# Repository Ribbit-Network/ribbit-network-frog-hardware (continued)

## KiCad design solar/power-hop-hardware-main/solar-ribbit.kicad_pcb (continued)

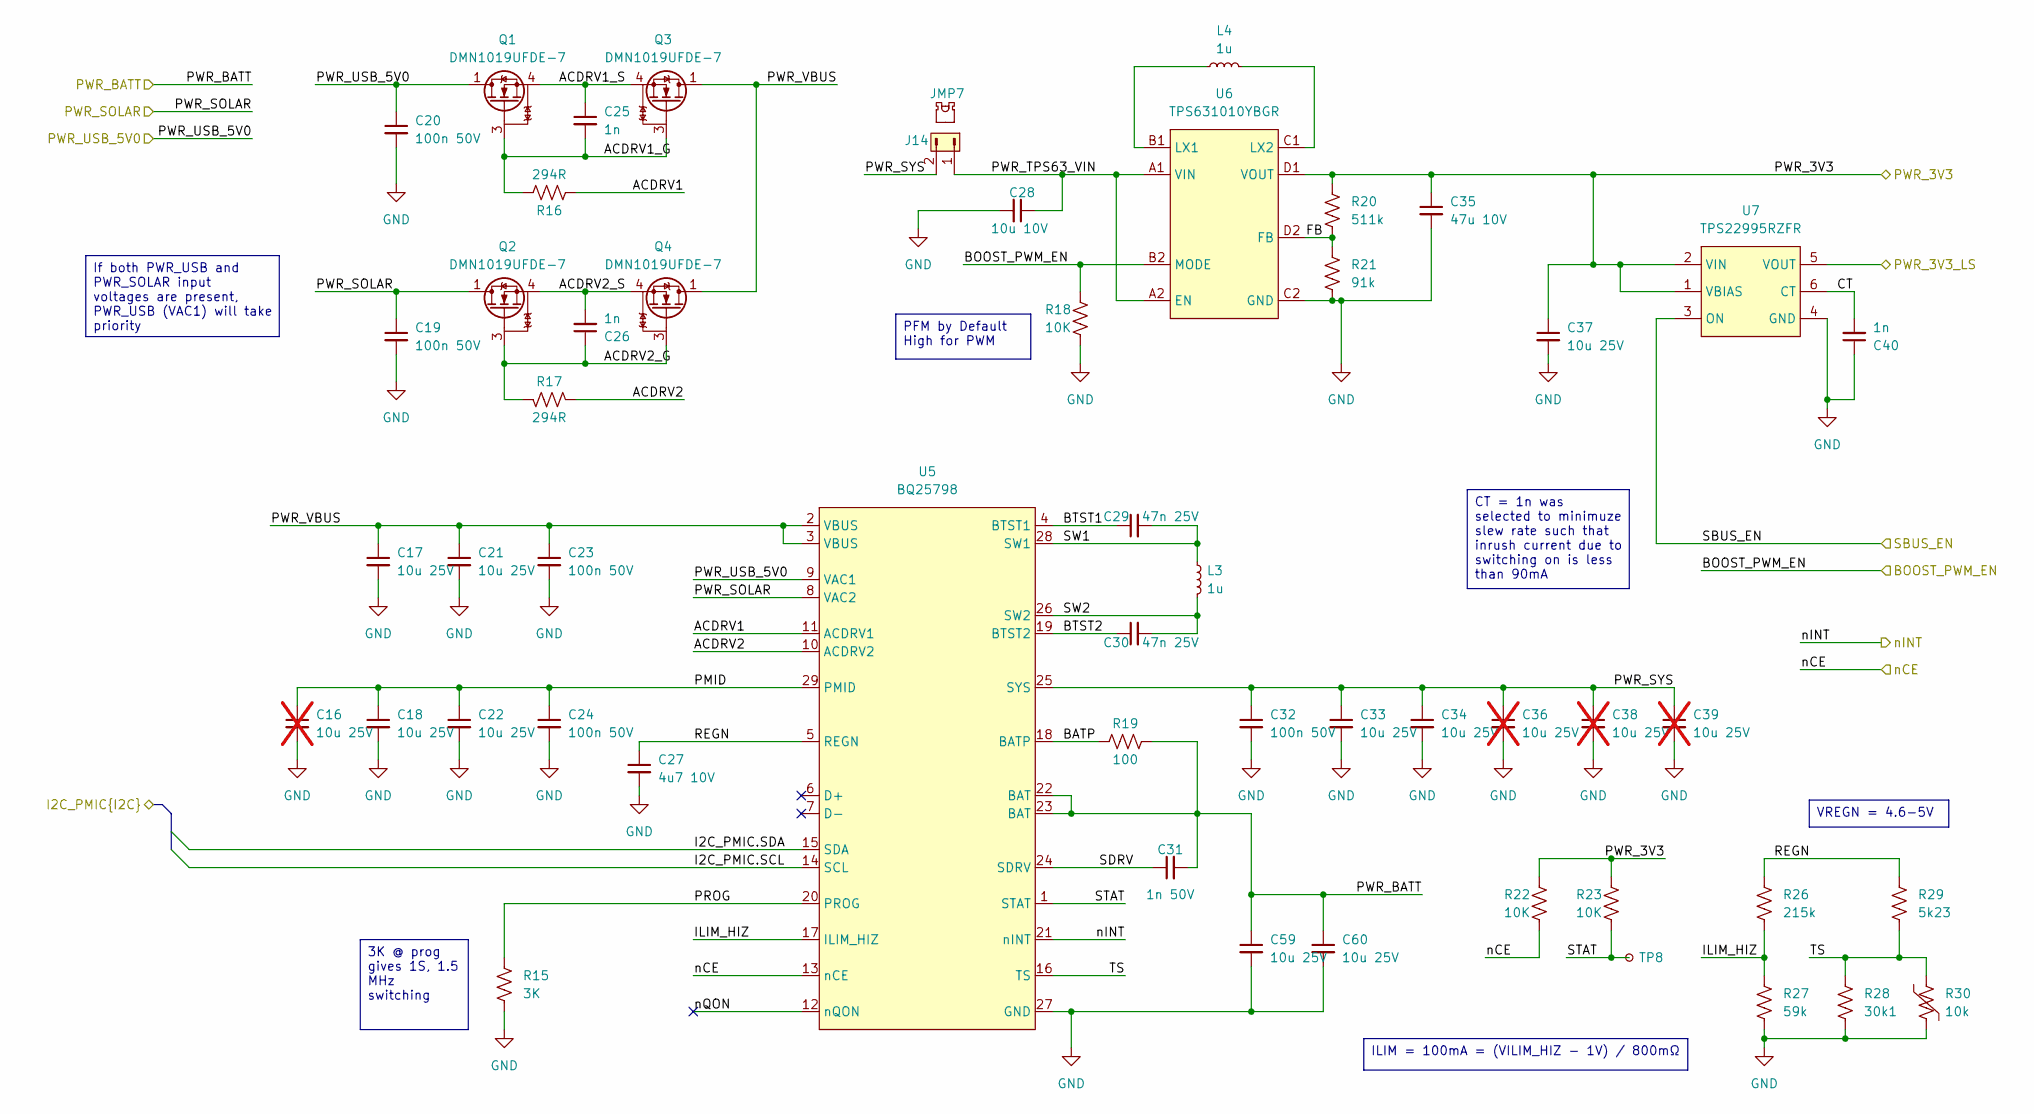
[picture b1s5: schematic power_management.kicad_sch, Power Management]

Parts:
C16, C36, C38, C39: 10u 25V; C_0805_2012Metric; MPN GRM21BR61E106KA73L; not fitted
C17, C18, C21, C22, C33, C34, C37, C59, C60: 10u 25V; C_0805_2012Metric; MPN GRM21BR61E106KA73L
C19, C20, C23, C24, C32: 100n 50V; C_0402_1005Metric; MPN GRM155R71H104KE14D
C25, C26, C40: 1n; C_0201_0603Metric; MPN GRM033R71E102KA01D
C27: 4u7 10V; C_0402_1005Metric; MPN GRM155R61A475MEAAD
C28: 10u 10V; C_0805_2012Metric; MPN C0805C106K8PACTU
C29, C30: 47n 25V; C_0402_1005Metric; MPN GRM155R71E473KA88D
C31: 1n 50V; C_0402_1005Metric; MPN GRM1555C1H102JA01D
C35: 47u 10V; C_0805_2012Metric; MPN GRM21BR61A476ME15K
J14: 10129380-902001BLF; PinHeader_1x02_P2.54mm_Vertical_SMD_Pin1Left; MPN 10129380-902001BLF
JMP7: QPC02SXGN-RC; MPN QPC02SXGN-RC
L3, L4: 1u; L_Taiyo-Yuden_MD-3030; MPN LSXND3030QKT1R0NNG
Q1, Q2, Q3, Q4: DMN1019UFDE-7; DI_DFN2020-6; MPN DMN1019UFDE-7
R15: 3K; R_0402_1005Metric; MPN ERJ-2RKF3001X
R16, R17: 294R; R_0402_1005Metric; MPN ERJ-2RKF2940X
R18, R22, R23: 10K; R_0402_1005Metric; MPN ERJ-2RKF1002X
R19: 100; R_0402_1005Metric; MPN ERJ-2RKF1000X
R20: 511k; R_0402_1005Metric; MPN CRCW0402511KFKEDC
R21: 91k; R_0402_1005Metric; MPN ERJ-2RKF9102X
R26: 215k; R_0402_1005Metric; MPN RC0402FR-07215KL
R27: 59k; R_0402_1005Metric; MPN RC0402FR-0759KL
R28: 30k1; R_0402_1005Metric; MPN RC0402FR-0730K1L
R29: 5k23; R_0402_1005Metric; MPN RC0402FR-075K23L
R30: 10k; R_0402_1005Metric; MPN NTCG103JF103FT1
TP8: TestPoint_Small; TestPoint_Pad_1.0x1.0mm; Part-DB ID 144
U5: BQ25798; TI_VQFN-HR-29; MPN BQ25798RQMR
U6: TPS631010YBGR; TI_DSBGA-8; MPN TPS631010YBGR
U7: TPS22995RZFR; TI_WQFN-6; MPN TPS22995RZFR

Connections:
/BOOST_PWM_EN: R18.1, U6.B2 (MODE); also elsewhere on the board
/BQ_nCE: R22.2, U5.13 (nCE); also elsewhere on the board
/BQ_nINT: U5.21 (nINT); also elsewhere on the board
/PWR_3V3: C35.1, C37.1, R20.1, R22.1, R23.1, U6.D1 (VOUT), U7.1 (VBIAS), U7.2 (VIN); also elsewhere on the board
/PWR_3V3_LS: U7.5 (VOUT); also elsewhere on the board
/PWR_BATT: C31.2, C59.1, C60.1, R19.2, U5.22 (BAT), U5.23 (BAT); also elsewhere on the board
/PWR_PANEL: C19.1, Q2.1 (D), U5.8 (VAC2); also elsewhere on the board
/PWR_USB: C20.1, Q1.1 (D), U5.9 (VAC1); also elsewhere on the board
/Power Management/ACDRV1: R16.2, U5.11 (ACDRV1)
/Power Management/ACDRV1_G: C25.2, Q1.3 (G), Q3.3 (G), R16.1
/Power Management/ACDRV1_S: C25.1, Q1.4 (S), Q3.4 (S)
/Power Management/ACDRV2: R17.2, U5.10 (ACDRV2)
/Power Management/ACDRV2_G: C26.1, Q2.3 (G), Q4.3 (G), R17.1
/Power Management/ACDRV2_S: C26.2, Q2.4 (S), Q4.4 (S)
/Power Management/BATP: R19.1, U5.18 (BATP)
/Power Management/BTST1: C29.1, U5.4 (BTST1)
/Power Management/BTST2: C30.1, U5.19 (BTST2)
/Power Management/CT: C40.2, U7.6 (CT)
/Power Management/FB: R20.2, R21.1, U6.D2 (FB)
/Power Management/I2C_PMIC.SCL: U5.14 (SCL); also elsewhere on the board
/Power Management/I2C_PMIC.SDA: U5.15 (SDA); also elsewhere on the board
/Power Management/ILIM_HIZ: R26.2, R27.1, U5.17 (ILIM_HIZ)
/Power Management/PMID: C16.1, C18.1, C22.1, C24.1, U5.29 (PMID)
/Power Management/PROG: R15.1, U5.20 (PROG)
/Power Management/PWR_SYS: C32.1, C33.1, C34.1, C36.1, C38.1, C39.1, J14.2, U5.25 (SYS)
/Power Management/PWR_TPS63_VIN: C28.1, J14.1, U6.A1 (VIN), U6.A2 (EN)
/Power Management/PWR_VBUS: C17.1, C21.1, C23.1, Q3.1 (D), Q4.1 (D), U5.2 (VBUS), U5.3 (VBUS)
/Power Management/REGN: C27.1, R26.1, R29.1, U5.5 (REGN)
/Power Management/SDRV: C31.1, U5.24 (SDRV)
/Power Management/STAT: R23.2, TP8.1, U5.1 (STAT)
/Power Management/SW1: C29.2, L3.1, U5.28 (SW1)
/Power Management/SW2: C30.2, L3.2, U5.26 (SW2)
/Power Management/TS: R28.1, R29.2, R30.1, U5.16 (TS)
/Power Management/nQON: U5.12 (nQON)
/SBUS_EN: U7.3 (ON); also elsewhere on the board
GND: C16.2, C17.2, C18.2, C19.2, C20.2, C21.2, C22.2, C23.2, C24.2, C27.2, C28.2, C32.2, C33.2, C34.2, C35.2, C36.2, C37.2, C38.2, C39.2, C40.1, C59.2, C60.2, R15.2, R18.2, R21.2, R27.2, R28.2, R30.2, U5.27 (GND), U6.C2 (GND), U7.4 (GND); also elsewhere on the board
unnamed: L4.1, U6.B1 (LX1)
unnamed: L4.2, U6.C1 (LX2)

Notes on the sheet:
ILIM = 100mA = (VILIM_HIZ - 1V) / 800mΩ
CT = 1n was selected to minimuze slew rate such that inrush current due to switching on is less than 90mA
If both PWR_USB and PWR_SOLAR input voltages are present, PWR_USB (VAC1) will take priority
VREGN = 4.6-5V
PFM by Default High for PWM
3K @ prog gives 1S, 1.5 MHz switching

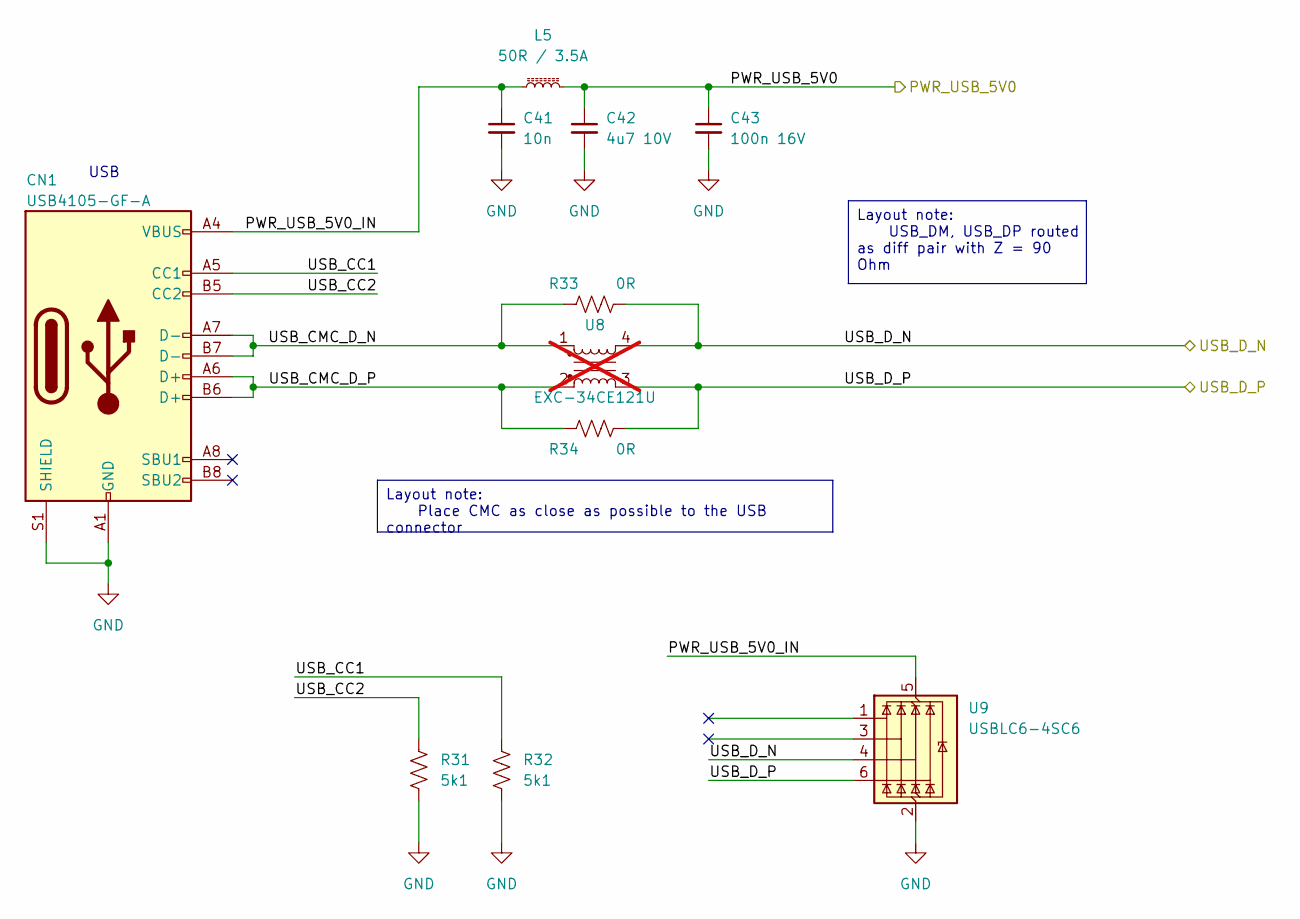
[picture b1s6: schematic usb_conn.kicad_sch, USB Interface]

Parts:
C41: 10n; C_0402_1005Metric; MPN CC0402KRX7R8BB103
C42: 4u7 10V; C_0402_1005Metric; MPN GRM155R61A475MEAAD
C43: 100n 16V; C_0402_1005Metric; MPN GRM155R71H104KE14D
CN1: USB4105-GF-A; GCT_USB4105-XX; MPN USB4105-GF-A
L5: 50R / 3.5A; L_1206_3216Metric; MPN BLM31PG500SN1L
R31, R32: 5k1; R_0402_1005Metric; MPN ERJ-2RKF5101X
R33, R34: 0R; R_0402_1005Metric; MPN ERJ-2GE0R00X
U8: EXC-34CE121U; PANASONIC_EXCX4CE; MPN EXC-34CE121U; not fitted
U9: USBLC6-4SC6; ST_SOT-23-6; MPN USBLC6-4SC6

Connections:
/PWR_USB_IN: C42.1, C43.1, L5.2; also elsewhere on the board
/USB/PWR_USB_5V0_IN: C41.1, CN1.A4 (VBUS), CN1.A9 (VBUS), CN1.B4 (VBUS), CN1.B9 (VBUS), L5.1, U9.5 (VBUS)
/USB/USB_CC1: CN1.A5 (CC1), R32.1
/USB/USB_CC2: CN1.B5 (CC2), R31.1
/USB/USB_CMC_D_N: CN1.A7 (D-), CN1.B7 (D-), R33.1, U8.1
/USB/USB_CMC_D_P: CN1.A6 (D+), CN1.B6 (D+), R34.1, U8.2
/USB/USB_D_N: R33.2, U8.4, U9.4 (I/O3); also elsewhere on the board
/USB/USB_D_P: R34.2, U8.3, U9.6 (I/O4); also elsewhere on the board
GND: C41.2, C42.2, C43.2, CN1.A1 (GND), CN1.A12 (GND), CN1.B1 (GND), CN1.B12 (GND), CN1.S1 (SHIELD), R31.2, R32.2, U9.2 (GND); also elsewhere on the board

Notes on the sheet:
USB
Layout note: USB_DM, USB_DP routed as diff pair with Z = 90 Ohm
Layout note: Place CMC as close as possible to the USB connector

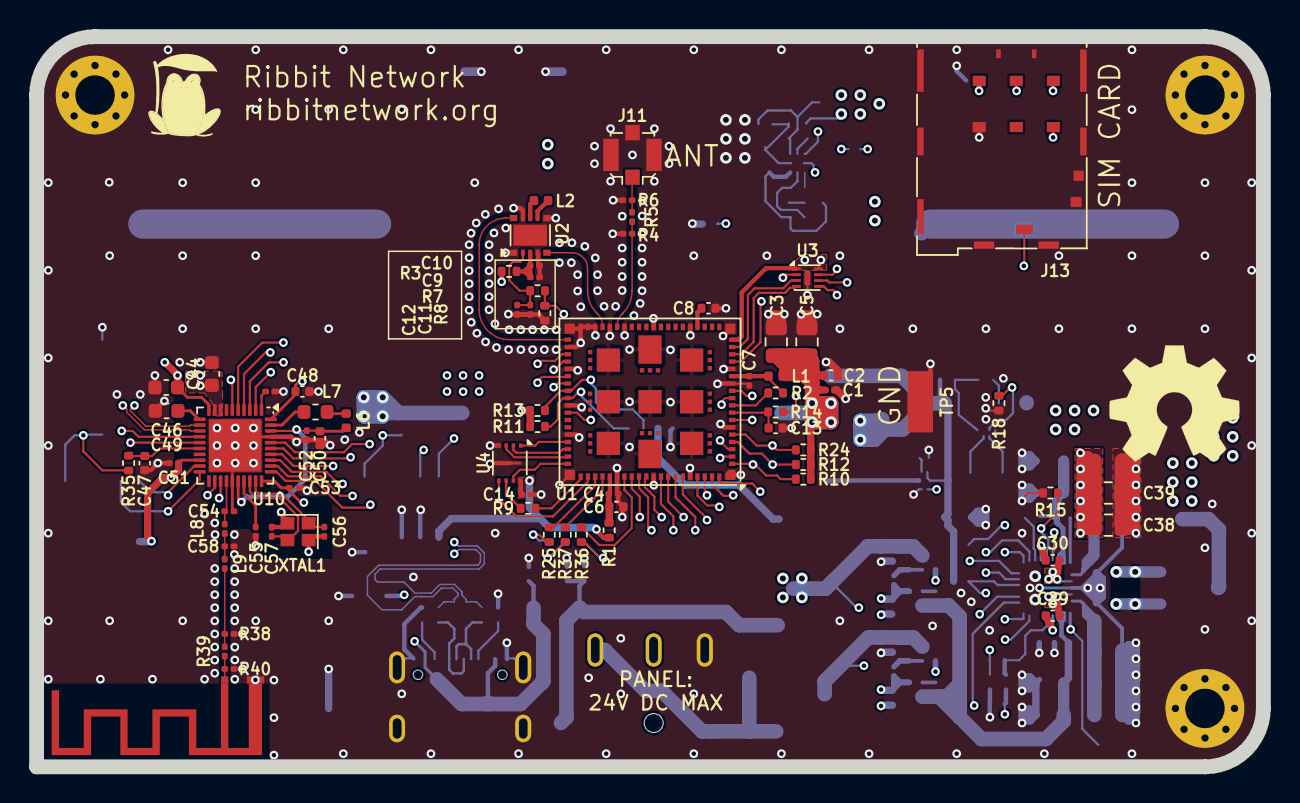
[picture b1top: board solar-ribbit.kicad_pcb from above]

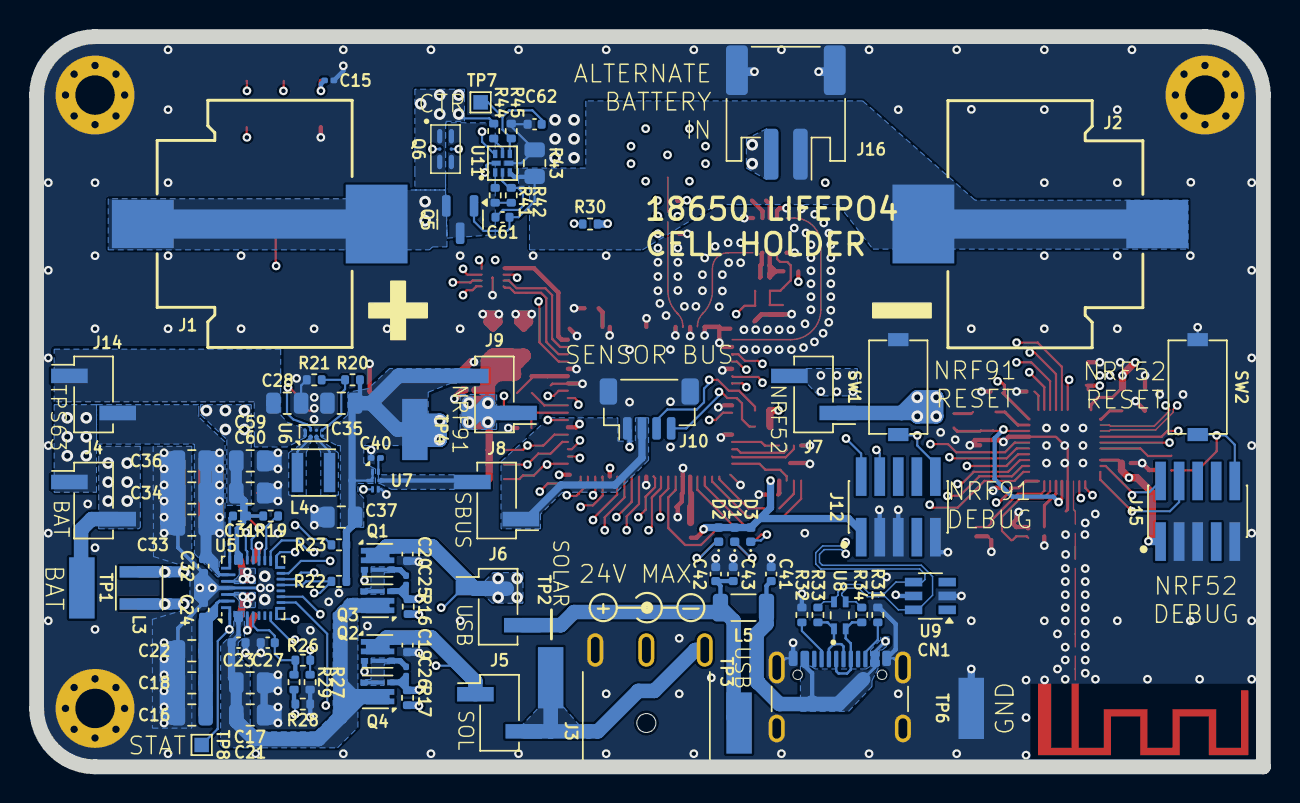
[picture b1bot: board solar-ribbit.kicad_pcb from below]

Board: 6 copper layers, 84.0 x 50.0 mm, 164 parts (92 on the bottom side), 128 nets.

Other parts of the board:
C1, C4, C7, C9, C12: 100n 16V; C_0201_0603Metric
C2: 1u 10V; C_0402_1005Metric
C3, C5: 47u 10V; C_0805_2012Metric
C6, C8: 4u7 10V; C_0402_1005Metric
C10, C11: 100p 50V; C_0201_0603Metric
J11: CONMHF1-SMD-G-T; TE_CONN_MHF1_SMD
L1: 120R / 2A; L_0402_1005Metric
L2: 9n1; L_0402_1005Metric
R1, R3, R7: 0R; R_0402_1005Metric
R2: 10K; R_0402_1005Metric
R4, R5, R6: 0R; R_0201_0603Metric
R8: 1M; R_0402_1005Metric
U2: SKY65943-11; SKY_MCM-10

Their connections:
/PWR_nRF91: C1.1, C2.1, C3.2, C5.2, L1.1, R1.1, R3.2; also elsewhere on the board
/nRF9151 - GPIO + UICC/LNA_EN: R7.1, R8.1; also elsewhere on the board
/nRF9151 - Power + RF/AMP_IN: L2.1, U2.8 (AMP_IN)
/nRF9151 - Power + RF/FIL_OUT: L2.2, U2.7 (FIL_OUT)
/nRF9151 - Power + RF/GNSS_LNA_RF: U2.10 (RF_OUT); also elsewhere on the board
/nRF9151 - Power + RF/GNSS_RF: U2.5 (RF_IN); also elsewhere on the board
/nRF9151 - Power + RF/LNA_EN_FILT: C11.1, C12.1, R7.2, U2.2 (VEN)
/nRF9151 - Power + RF/LNA_VCC_IN: C9.1, C10.1, R3.1, U2.3 (VCC)
/nRF9151 - Power + RF/LTE_ANT: J11.1 (In), R5.2, R6.2
/nRF9151 - Power + RF/LTE_ANT_TUNED: R4.2, R5.1; also elsewhere on the board
/nRF9151 - Power + RF/nRF91_VDD: C7.1, L1.2, R2.1; also elsewhere on the board
/nRF9151 - Power + RF/nRF91_VDD_GPIO: C4.1, C6.1, R1.2; also elsewhere on the board
GND: C1.2, C2.2, C3.1, C4.2, C5.1, C6.2, C7.2, C8.2, C9.2, C10.2, C11.2, C12.2, J11.2 (Ext), R4.1, R6.1, R8.2, U2.1 (GND), U2.4 (GND), U2.6 (GND), U2.9 (GND), U2.11 (GND); also elsewhere on the board
unnamed 124: C8.1; also elsewhere on the board
unnamed 125: R2.2; also elsewhere on the board

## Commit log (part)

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2021-09-09 Fix typos in assembly docs
2021-09-10 Updated mechanical parts for release
2021-09-12 Add links to Need Help
2021-09-12 Add an alt BOM with Canadian suppliers
    This is an alternative Bill of Materials for people purchasing
    in Canada. Purchasing from the US is often more expensive, can
    take much longer to ship (depending on courier), and usually
    requires paying extra customs/import fees.
2021-09-16 fixed one more link title
2021-09-16 Fixed another link
2021-09-16 added another clarification to instructions document
2021-09-16 Deleted deprecated mqtt docker image
2021-09-16 Added some more build pictures
2021-09-21 #48 Added a note about placing in the shade
2021-09-21 #49 Added Loctite images
2021-10-06 Removed 32 bit RPI 3
2021-10-11 Added BOM links for UK
2021-11-04 Small space removal
2021-11-09 Adjusted main image size
2021-11-09 Fixed international bom typo
2021-11-10 #40 #56 Added Debugging FAQ
2021-11-12 docs: update README.md [skip ci]
2021-11-12 docs: create .all-contributorsrc [skip ci]
2021-11-16 Added chat icon
2021-11-19 Downgrade Debian to track official Beaglebone image
2021-11-20 Enable i2c-gpio on rasbperry pi
    This change enables i2c-gpio (software i2c) for raspberry pi boards instead of the hardware i2c to work around a bug in the clock stretching in hardware i2c. Clock stretching is required by the co2 s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
2021-12-07 Added BOM for V2
2021-12-07 Fixed link to build instructions
2021-12-11 #62 Replace Beaglebone Black with Beaglebone Green Gateway
2021-12-11 Update BB Green Gateway BOM Name
2022-01-09 [software/co2] Python devenv
2022-01-09 [software/co2] Dockerfile: Upgrade pip, hopefully makes us not need a Rust compiler
2022-01-09 [software/co2] Dockerfile: PEP 517 to the rescue
2022-01-09 [software/co2] Remove unused dependencies
2022-01-09 [software/co2] f-strings are Good (TM)
2022-01-10 [software/co2] Try to use the correct i2c bus
2022-01-10 [software/co2] Rought draft for I2C GPS provider
2022-01-10 [software/co2] Let's get some timestamps in the output
2022-01-11 [software/co2] Add support for reading GPS over I2C (#93)
    Refactor co2.py to allow multiple GPS provider implementations
    Add a GPS implementation using I2C
    Add a dummy GPS implementation
    Keep the GPSD implementation for backwards compatibility
    Sets up the logging module and uses it for all output (Timestamps Are Good (TM))
2022-01-11 docs: add abesto as a contributor for code (#94)
    * docs: update README.md [skip ci]
    * docs: update .all-contributorsrc [skip ci]
2022-01-13 [software/co2] Shrink Docker image using multi-stage build
    ... and also by dropping some unused dependencies
2022-01-14 [software/gpsd] Port improvements from software/co2
2022-01-19 V2 BOM: Corrected power supply link
2022-01-19 V2 BOM: Updated brass standoffs
2022-01-19 [software] README: Add notes on co2, gpsd devenv
2022-01-21 GPS: Renamed GPS service for static analysis
2022-01-21 Updated readme for gps service rename
2022-01-21 GPS: Renamed GPS service for static analysis (#100)
    * GPS: Renamed GPS service for static analysis
    * Updated readme for gps service rename
2022-01-22 Adding images
2022-01-22 page 1
2022-01-22 part 2
2022-01-22 fixed v1
2022-01-22 Added all the v2 images
2022-01-22 fixed link
2022-01-22 Fixed readme link
2022-01-24 Fixed gps image on v2 debugging guide
2022-01-25 Updated BOM standoffs
2022-01-26 #101 Improved readme about influxdb config
2022-02-06 Updated balena configuration to support bbgw
2022-02-10 Add balena_image_download.png
2022-04-01 Create test.txt
    getting the directory setup
2022-04-05 Updated balena.yml with better instruction
2022-04-14 Corrected balena.yml
    The correct device type for BBG Wireless is beaglebone-green-wifi
2022-04-16 Corrected balena.yml (#118)
    The correct device type for BBG Wireless is beaglebone-green-wifi
2022-05-06 #120 Update sponsor button
2022-05-18 fixed typo building
2022-05-31 Update 7-sensor-placement.md
    Add note about enclosures for supplying outdoor power
2022-08-04 V3 Frog: Updated BOM
2022-08-09 boilerplate ts express.js
2022-08-09 building a container now =
2022-08-09 adds sqlite connection
2022-08-09 platform UUID
2022-08-10 adds basic authentication options
2022-08-10 configuration page
2022-08-11 finish page
2022-08-19 gitignore
2022-08-19 thinking about volumes...
2022-08-28 #134 added v2 images and instructions for updates
2022-08-31 adds the endpoint
2022-08-31 Image and STL Upload
    Uploaded the V3 images and the V3 STL files to the V3 mechanical folder
2022-09-01 V3 BOM: Increased cable length to 200 mm #142
2022-09-01 Edits to the assembly instructions
    Reviewed the assembly instructions and needed to make some edits to correct errors.
2022-09-01 Image Link Update
    One last image link update
2022-09-19 #148 Fixed broken debugging link
2022-09-21 Readme Edits for V3
2022-09-21 Readme Edits for V3 (#151)
    * Readme Edits for V3
2022-09-27 Update BOM
    Updated BOM to include the 50mm, 100mm, and 200mm cables.
2022-09-27 Add step Carrier Board assembly
    Added a step to show the Pi4 compute module snapping into the carrier board.
2022-09-27 Fixed V2 typo to V3
    Fixed V2 typo to V3
2022-09-28 Moving Commits from the v3_instructions to the main (#153)
    * Update README.md
    V2 -> V3 edits in readme
    * Update BOM
    Updated BOM to include the 50mm, 100mm, and 200mm cables.
    * Update BOM V3
    Updated the power supply in the BOM for V3. Changed to a Raspberry Pi model with USB-c.
2022-09-28 Fixed Broken Link
    Broken link to international BOMs. Fixed in V2 and V3 Readme files.
2022-09-30 Updated Readme Frog Pic
2022-10-01 Example files for golioth esp32
2022-10-01 Add esp32 workflow triggers
2022-10-01 Changed github actions to esp32
2022-10-05 Fixing Broken Link related to issue #154 (#155)
    Added info around helping create international BOMs and created folders for each version.
2022-10-06 Build esp-idf-lib
2022-10-06 Update README.md
    added link to code of conduct
2022-10-08 App compiles with scd30 driver linked
2022-10-09 adding required tools section
2022-10-10 Update README.md
    updated link to code of conduct with the public link.
2022-10-11 adding tools section to instructions
2022-10-18 #126 switched esp32 board to s3
2022-10-18 Adding vscode workspace file
2022-10-18 Added basic i2c power switch
2022-10-18 International BOM Folder
    Created an international_boms folder in V3
2022-10-19 Image Update and International BOM link fix. (#176)
    * International BOM Folder
    Created an international_boms folder in V3
    * Update balena_image_download.png
    Updated the image to show the Raspberry Pi CM4 IO Board selection
2022-10-20 Update 3-software.md
    Added pictures of inserting the SD card and changed the section about inserting the SD card from Beaglebone focused to Raspberry Pi focused.
2022-10-24 PR to address Issue #160 and #170 (#177)
    Added pictures of inserting the SD card and changed the section about inserting the SD card from Beaglebone focused to Raspberry Pi focused.
    * Assembly Instructions Update
    Added a step with pictures to explain how to clip the antenna cable onto the CM4.
2022-10-24 not checking error of void function
2022-10-25 docs: add akhilgupta1093 as a contributor for code (#180)
    * docs: update README.md [skip ci]
    * docs: update .all-contributorsrc [skip ci]
2022-11-27 Moved Sensors Version Number to Top Level Directories
2022-11-27 Update git submodule path for new dir stucture
2022-11-27 fixed submodules
2022-11-27 #152 V3: Switch default GPS source
    Also removes gps container for v3 sensors
2022-11-27 Update software link
2022-11-27 #152 V3: Switch default GPS source (#183)
    * Also removes gps container for v3 sensors
    * Update software link in V3 build instructions
2022-11-27 #106 V2: Removed GPS on v2 sensor (i2c-gps)
2022-11-27 Adding frog software for lab testing
    Switches to new influx credentials and removes gps reads
    bucket=lab-testing
    url=https://us-central1-1.gcp.cloud2.influxdata.com
    org=keenan@ribbitnetwork.org
2022-11-27 Adding workspace file
2022-11-27 Added CONFIG_ESP_CONSOLE_USB_SERIAL_JTAG=y
2022-11-27 first version of esp32 working skeleton
2022-11-27 scd30 lib links correctly
2022-11-27 Added github workflow for esp32s3 build
2022-11-27 Frog V4: Esp32s3 with SCD30 and Golioth Support (#184)
    * Adding basics of esp32s3 project that connects to golioth
    * Adding workspace file for esp-idf vscode extension
    * Added github workflow for esp32s3 build
    * Added sensor driver support for scd30
2022-11-30 initial integration of gps
2022-12-06 #178 V3 Instructions: Added solder iron
2022-12-07 integrating gps fully
2022-12-09 [WIP] esp-idf Gps integration (#189)
    * Initial integration of gps
    * Adding comments to fix race conditions
    Note that this code is currently non-functional due to a bug noted in https://github.com/Ribbit-Network/ribbit-network-frog-hardware/pull/189
    However, we don't currently plan on using the esp-idf implementation as we moved to a micropython based implementation in https://github.com/Ribbit-Network/ribbit-network-frog-software
2022-12-09 V4: Initial mechanical parts, instructions framework and BOM
2022-12-09 hook mechanisms
2022-12-09 deleted files
2022-12-09 docs: add muditprotect3d as a contributor for design (#193)
    * docs: update README.md [skip ci]
    * docs: update .all-contributorsrc [skip ci]
2022-12-11 Update assembly-instructions documents for V4
    Updated each file in the assembly-instructions folder for V4 of the sensor.
2022-12-14 Update assembly-instructions documents for V4 (#194)
    * Update assembly-instructions documents for V4
    Updated each file in the assembly-instructions folder for V4 of the sensor.
    * Updated BOM for V4
    Updated BOM for V4
2023-01-05 V4: Add zip ties to BOM
2023-01-05 V4: Add Zip ties to BOM (#196)
2023-01-06 Update number in instruction pages
2023-01-06 Removed international BOM section
2023-01-07 Removed kofi links
2023-01-10 Add curl instructions for windows
2023-01-19 Adding updated V4 mechanical files
2023-02-19 Updated Assembly Instructions
    Updated instructions to account for the changes made to the base of V4. Also added some pictures of the various hanging options.
2023-03-28 Github Actions: Remove SW Builds
2023-03-29 Removed zip ties
2023-04-02 Updated Assembly Instructions
    Edits to #3 and #4 to add more specifics.
2023-05-21 Update Instructions
    Added details to the credentials section of the software instructions.
    Added a link to an Adafruit wishlist in the parts sections and an explanation on how to load that wishlist into your cart.
2023-05-23 Update README.md with Get Involved Section
2023-05-28 The basics of MkDocs are running
2023-05-28 Add PR to docs build
2023-05-29 Removed pr build
2023-05-30 mkdocs work
2023-06-11 Testing branch preview deploy
2023-06-11 Add finished Frog Gif
2023-06-11 Fix adafruit link
2023-06-11 Update Frog Cover Photo
2023-06-16 README.md: Fix links to old versions
2023-06-16 2-3d-printing.md: Fix link to mech parts
2023-06-16 1-parts.md: Fix bom linnk
2023-06-24 Updated Lid part file
    Added the most updated lid file. Tightened tolerance so that the lid is not loose.
2023-06-29 Instructions: Add Gifs to Placement #217
2023-06-29 Instructions: Add Gifs to Placement #217 (#222)
2023-08-25 Fix grammar/typos in software.md
2023-08-28 fix typo
2023-08-29 Docs: Added Sensor Testing Step
2023-08-29 Docs: Added parts descriptions
2025-05-31 Update dev links to slack
2025-05-31 Update link to software
2025-05-31 Deployed f312218 with MkDocs version: 1.6.1
2025-08-20 Solar Initial Commit (#238)
    * Create README.txt
    * Add Desmond's files from hackster competition
    https://github.com/djgood/power-hop-hardware/tree/main
2025-09-10 Add overviews, bom, test plan drafts to readme
